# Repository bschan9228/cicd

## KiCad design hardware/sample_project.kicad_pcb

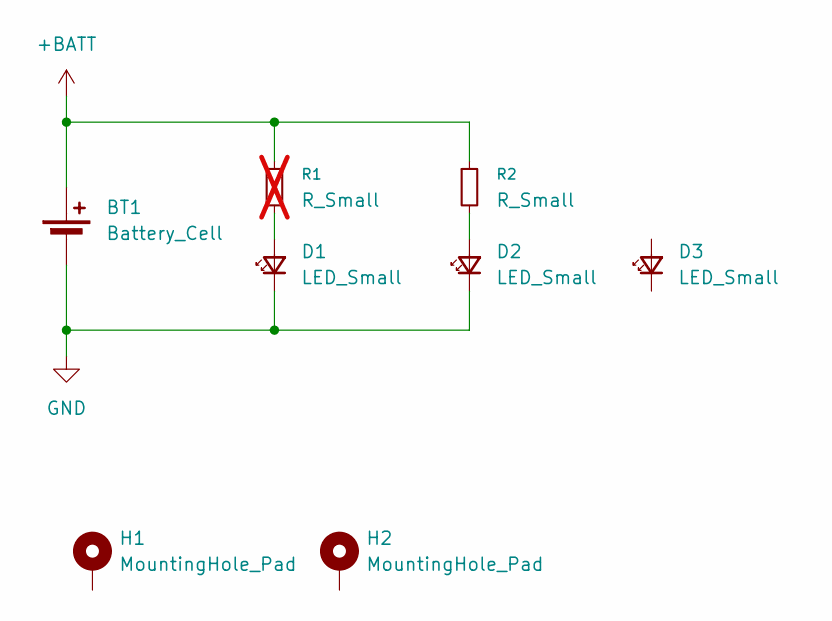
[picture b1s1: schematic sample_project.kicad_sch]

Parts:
BT1: Battery_Cell; BatteryHolder_Keystone_1060_1x2032
D1, D3: LED_Small; LED_0805_2012Metric
D2: LED_Small; LED_D3.0mm
H1, H2: MountingHole_Pad; MountingHole_3.2mm_M3_Pad_Via
R1: R_Small; R_0805_2012Metric; not fitted
R2: R_Small; R_Axial_DIN0207_L6.3mm_D2.5mm_P10.16mm_Horizontal

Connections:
+BATT: BT1.1 (+), R1.1, R2.1
GND: BT1.2 (-), D1.1 (K), D2.1 (K)
unnamed: D1.2 (A), R1.2
unnamed: D2.2 (A), R2.2

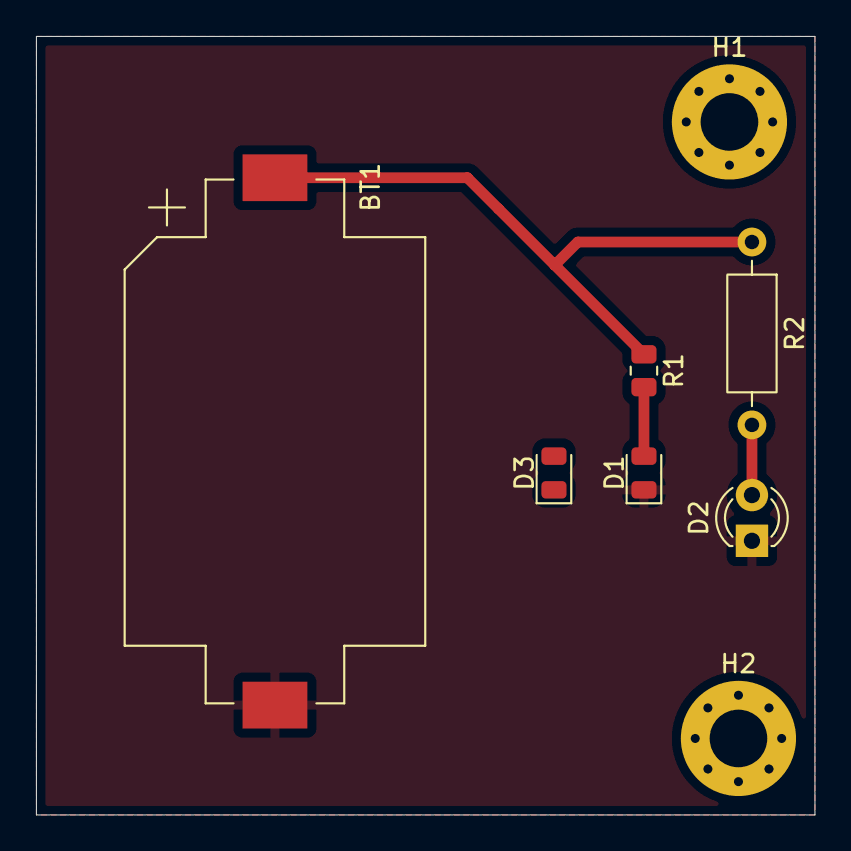
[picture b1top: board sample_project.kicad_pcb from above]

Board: 2 copper layers, 43.2 x 43.2 mm, 8 parts (0 on the bottom side), 4 nets.

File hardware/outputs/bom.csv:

"Reference","Value","Part Number","Footprint","DNP"
"BT1","Battery_Cell","","Battery:BatteryHolder_Keystone_1060_1x2032",""
"D1,D3","LED_Small","","LED_SMD:LED_0805_2012Metric",""
"D2","LED_Small","","LED_THT:LED_D3.0mm",""
"R1","R_Small","","Resistor_SMD:R_0805_2012Metric","DNP"
"R2","R_Small","","Resistor_THT:R_Axial_DIN0207_L6.3mm_D2.5mm_P10.16mm_Horizontal",""

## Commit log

2026-03-08 Updated exporting script
2026-03-08 fix kicad workflow
2026-03-09 Updated workflows again
    Fixed file exist workflow
    added space to file exist workflow
    Updated fie exist again
    file exist env variable
    updated file exist
    Updated file exist workflow
2026-03-09 Fixed file exist workflow
2026-03-12 removed csv from gitignore
2026-03-12 changed position units to mm
2026-03-12 bom footprint grouping
